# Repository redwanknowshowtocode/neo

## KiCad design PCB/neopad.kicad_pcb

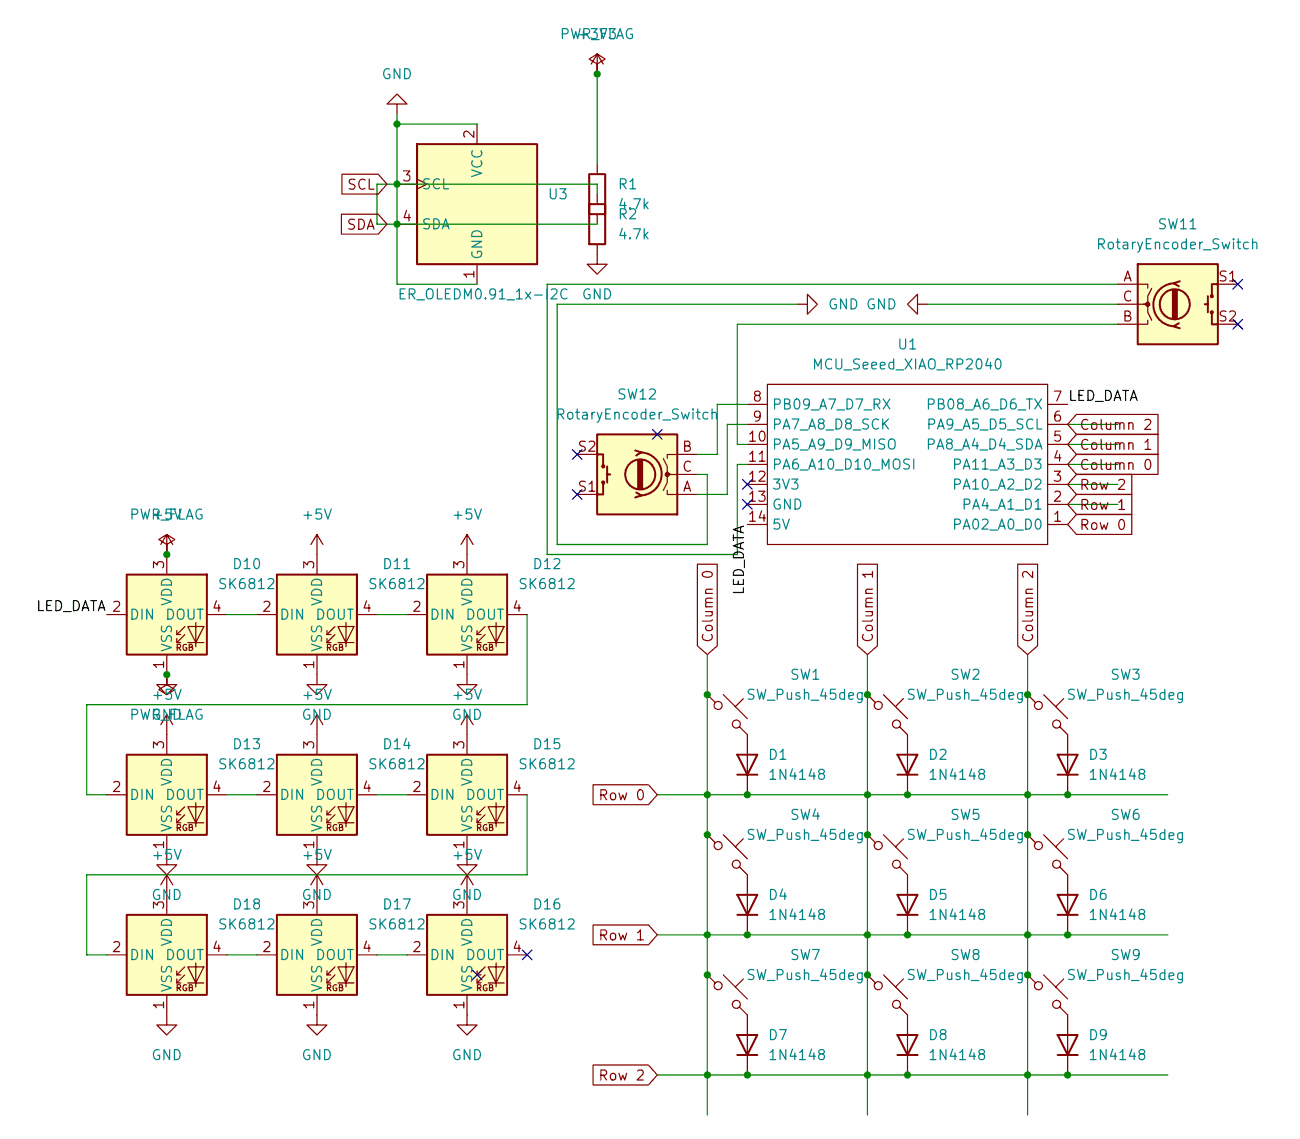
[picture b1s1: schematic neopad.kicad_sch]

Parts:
D1, D2, D3, D4, D5, D6, D7, D8, D9: 1N4148; D_DO-35_SOD27_P7.62mm_Horizontal
D10, D11, D12, D13, D14, D15, D16, D17, D18: SK6812; LED_SK6812_PLCC4_5.0x5.0mm_P3.2mm
R1, R2: 4.7k; R_Axial_DIN0207_L6.3mm_D2.5mm_P7.62mm_Horizontal
SW1, SW2, SW3, SW4, SW5, SW6, SW7, SW8, SW9: SW_Push_45deg; SW_Cherry_MX_1.00u_Plate
SW11, SW12: RotaryEncoder_Switch; RotaryEncoder_Alps_EC11E-Switch_Vertical_H20mm
U1: MCU_Seeed_XIAO_RP2040; XIAO-RP2040-SMD
U3: ER_OLEDM0.91_1x-I2C

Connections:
+3V3: R1.1
+5V: D10.3 (VDD), D11.3 (VDD), D12.3 (VDD), D13.3 (VDD), D14.3 (VDD), D15.3 (VDD), D16.3 (VDD), D17.3 (VDD), D18.3 (VDD)
/LED_DATA: D10.2 (DIN), U1.7 (PB08_A6_D6_TX), U1.14 (5V)
Column 0: D1.1 (K), D2.1 (K), D3.1 (K), D4.1 (K), D5.1 (K), D6.1 (K), D7.1 (K), D8.1 (K), D9.1 (K), SW1.1, SW2.1, SW3.1, SW4.1, SW5.1, SW6.1, SW7.1, SW8.1, SW9.1, U1.1 (PA02_A0_D0), U1.2 (PA4_A1_D1), U1.3 (PA10_A2_D2), U1.4 (PA11_A3_D3), U1.5 (PA8_A4_D4_SDA), U1.6 (PA9_A5_D5_SCL)
unnamed: D1.2 (A), SW1.2
unnamed: D2.2 (A), SW2.2
unnamed: D3.2 (A), SW3.2
unnamed: D4.2 (A), SW4.2
unnamed: D5.2 (A), SW5.2
unnamed: D6.2 (A), SW6.2
unnamed: D7.2 (A), SW7.2
unnamed: D8.2 (A), SW8.2
unnamed: D9.2 (A), SW9.2
unnamed: D10.4 (DOUT), D11.2 (DIN)
unnamed: D11.4 (DOUT), D12.2 (DIN)
unnamed: D12.4 (DOUT), D13.2 (DIN)
unnamed: D13.4 (DOUT), D14.2 (DIN)
unnamed: D14.4 (DOUT), D15.2 (DIN)
unnamed: D15.4 (DOUT), D18.2 (DIN)
unnamed: D16.2 (DIN), D17.4 (DOUT)
unnamed: D17.2 (DIN), D18.4 (DOUT)
unnamed: SW11.B, U1.10 (PA5_A9_D9_MISO)
unnamed: SW11.A, U1.11 (PA6_A10_D10_MOSI)
unnamed: SW12.A, U1.9 (PA7_A8_D8_SCK)
unnamed: SW12.B, U1.8 (PB09_A7_D7_RX)
SCL: D10.1 (VSS), D11.1 (VSS), D12.1 (VSS), D13.1 (VSS), D14.1 (VSS), D15.1 (VSS), D16.1 (VSS), D17.1 (VSS), D18.1 (VSS), R1.2, R2.1, R2.2, SW11.C, SW12.C, U3.1 (GND), U3.2 (VCC), U3.3 (SCL), U3.4 (SDA)

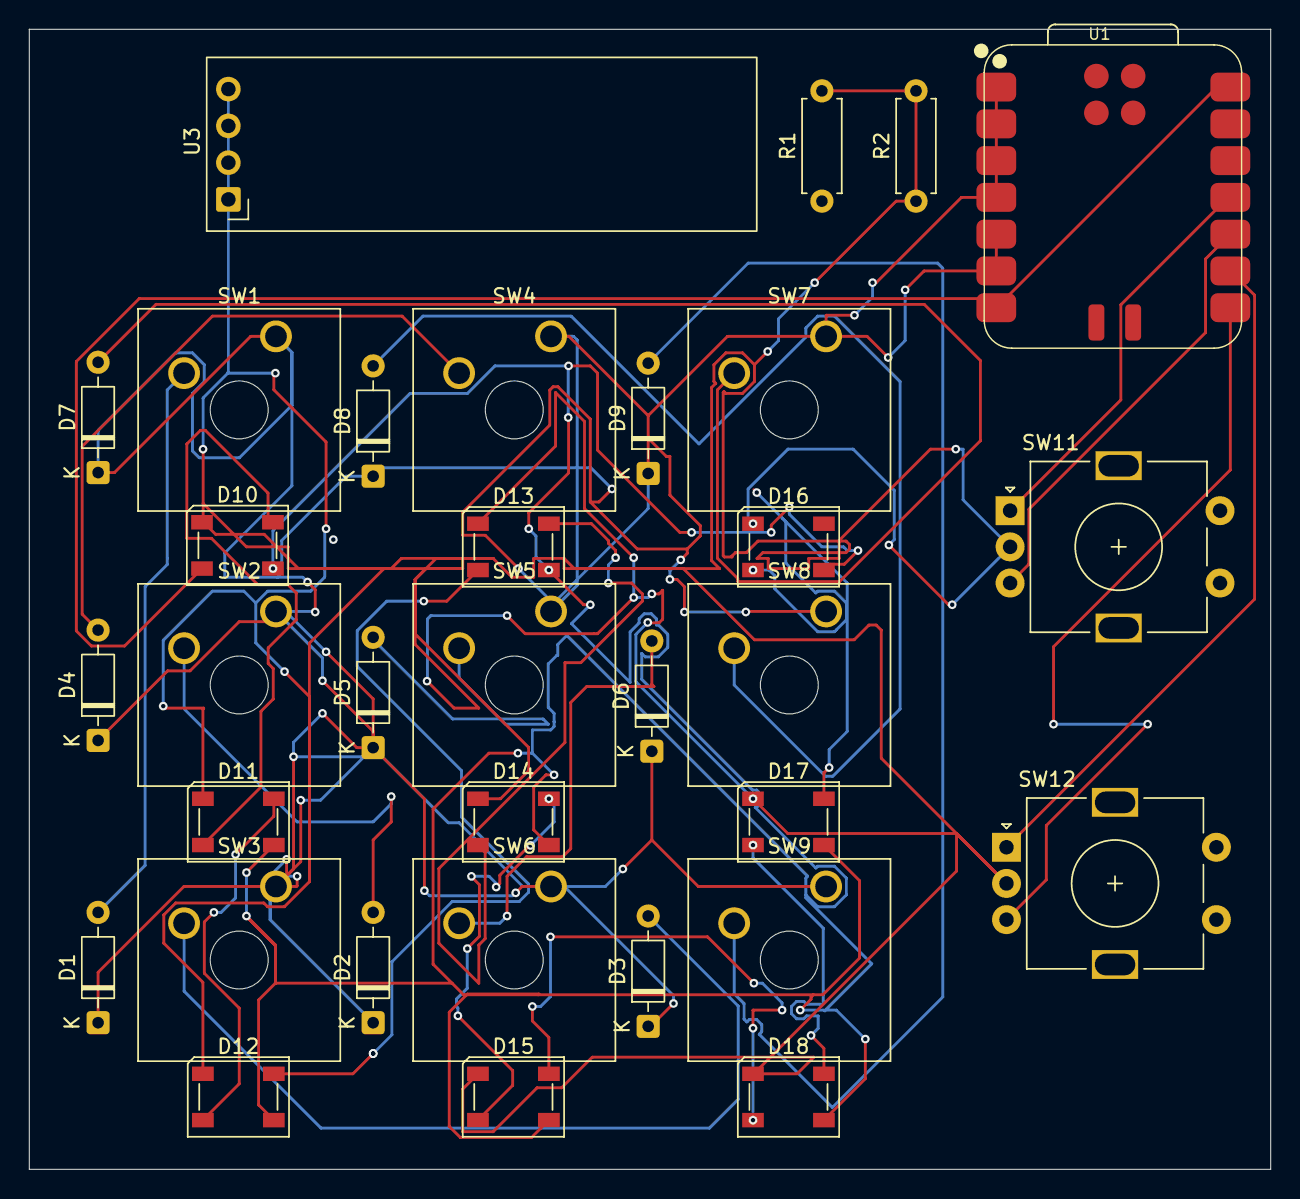
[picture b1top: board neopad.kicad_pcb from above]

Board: 2 copper layers, 85.8 x 78.8 mm, 33 parts (0 on the bottom side), 25 nets.

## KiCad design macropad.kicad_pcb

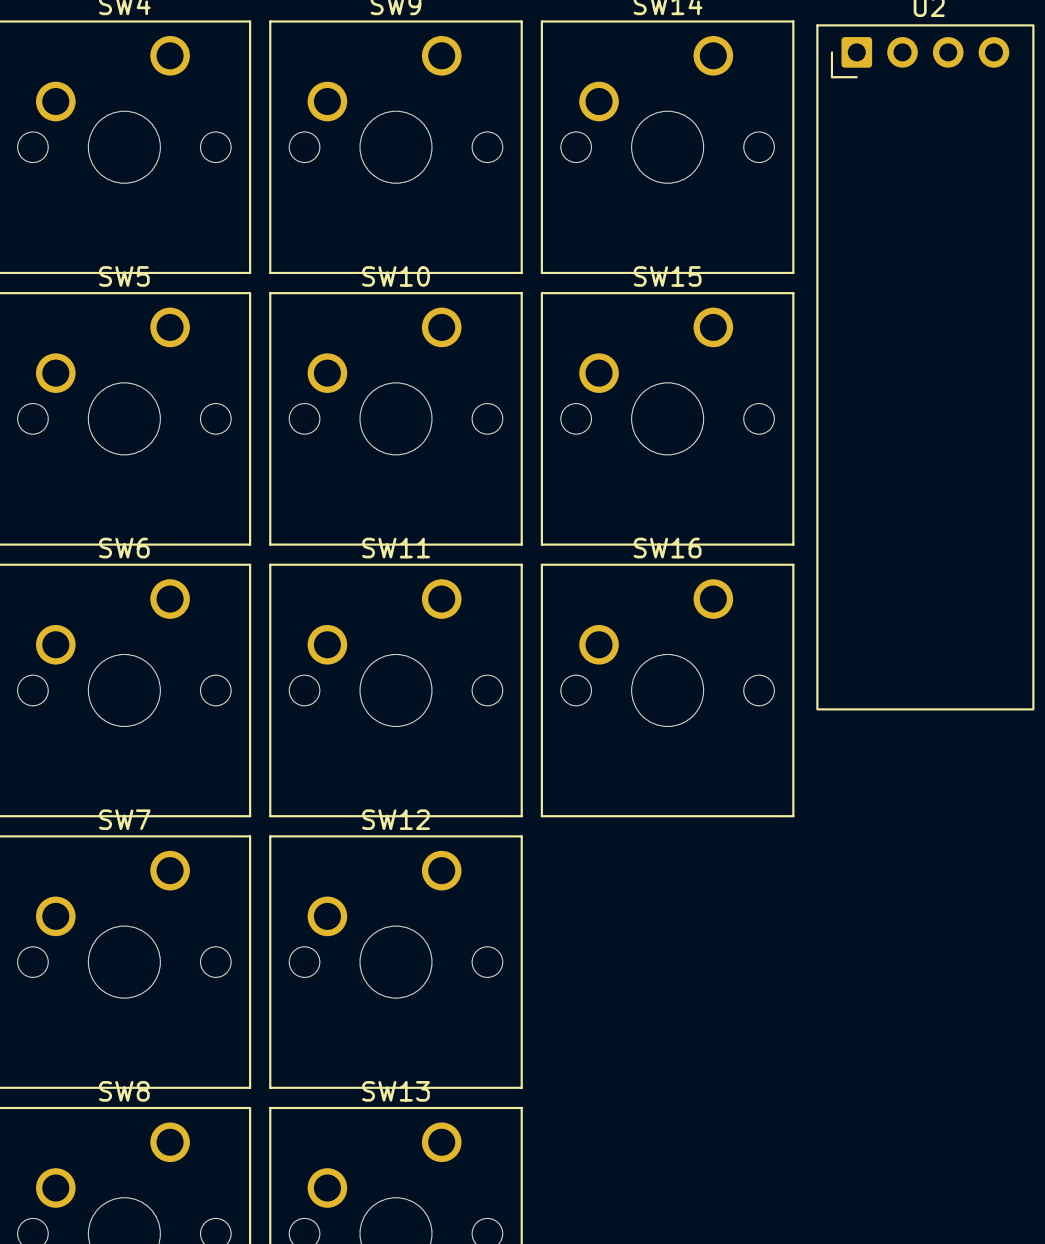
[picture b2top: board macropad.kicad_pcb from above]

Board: 2 copper layers, 14 parts (0 on the bottom side), 4 nets, no tracks yet.

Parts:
SW4, SW5, SW6, SW7, SW8, SW9, SW10, SW11, SW12, SW13, SW14, SW15, SW16: SW_Push; SW_Cherry_MX_1.00u_PCB
U2: ER_OLEDM0.91_1x-I2C

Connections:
unnamed: SW6.2 (2_2), SW10.1
unnamed: SW9.2 (2_2), SW10.2, SW11.2 (2_2), SW12.2
unnamed: SW7.2 (2_2), SW8.2 (2_2), SW12.1
unnamed: SW13.2 (2_2), SW14.2 (2_2), SW15.2 (2_2), SW16.2 (2_2)

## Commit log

2026-04-21 Rename project from 'custom-macropad' to 'neopad'
2026-04-21 Fix formatting of project name in README
2026-05-18 Rename 'pcd design' to 'PCB'
2026-05-18 Add kanye file
2026-05-18 Add PCB folder
2026-05-23 Rename .step to neopcb.step
